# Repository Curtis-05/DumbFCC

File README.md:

<h1 align="center">Dumb FCC</h1>

<p align="center" width="100%">
  
</p>

***

<p align="center">
  
&nbsp; &nbsp; &nbsp; &nbsp;
  
</p>

***

## SPECIFICATIONS

| Parameter | Value | 
| --- | --- |
| Dimensions | 70.0 × 50.0 mm |

***

## DIRECTORY STRUCTURE

    .
    ├─ Computations       # Misc calculations
    ├─ HTML               # HTML files for generated webpage
    ├─ Images             # Pictures and renders
    │
    ├─ kibot_resources    # External resources for KiBot
    │  ├─ colors          # Color theme for KiCad
    │  ├─ fonts           # Fonts used in the project
    │  ├─ scripts         # External scripts used with KiBot
    │  └─ templates       # Templates for KiBot generated reports
    │
    ├─ kibot_yaml         # KiBot YAML config files
    ├─ KiRI               # KiRI (PCB diff viewer) files
    │
    ├─ lib                # KiCad footprint and symbol libraries
    │  ├─ 3d_models       # Component 3D models
    │  ├─ lib_fp          # Footprint libraries
    │  └─ lib_sym         # Symbol libraries
    │
    ├─ Logos              # Logos
    │
    ├─ Manufacturing      # Assembly and fabrication documents
    │  ├─ Assembly        # Assembly documents (BoM, pos, notes)
    │  │
    │  └─ Fabrication     # Fabrication documents (ZIP, notes)
    │     ├─ Drill Tables # CSV drill tables
    │     └─ Gerbers      # Gerbers
    │
    ├─ Report             # Reports for ERC/DRC
    ├─ Schematic          # PDF of schematic
    ├─ Templates          # Title block templates
    ├─ Testing
    │  └─ Testpoints      # Testpoints tables      
    │
    └─ Variants           # Outputs for assembly variants

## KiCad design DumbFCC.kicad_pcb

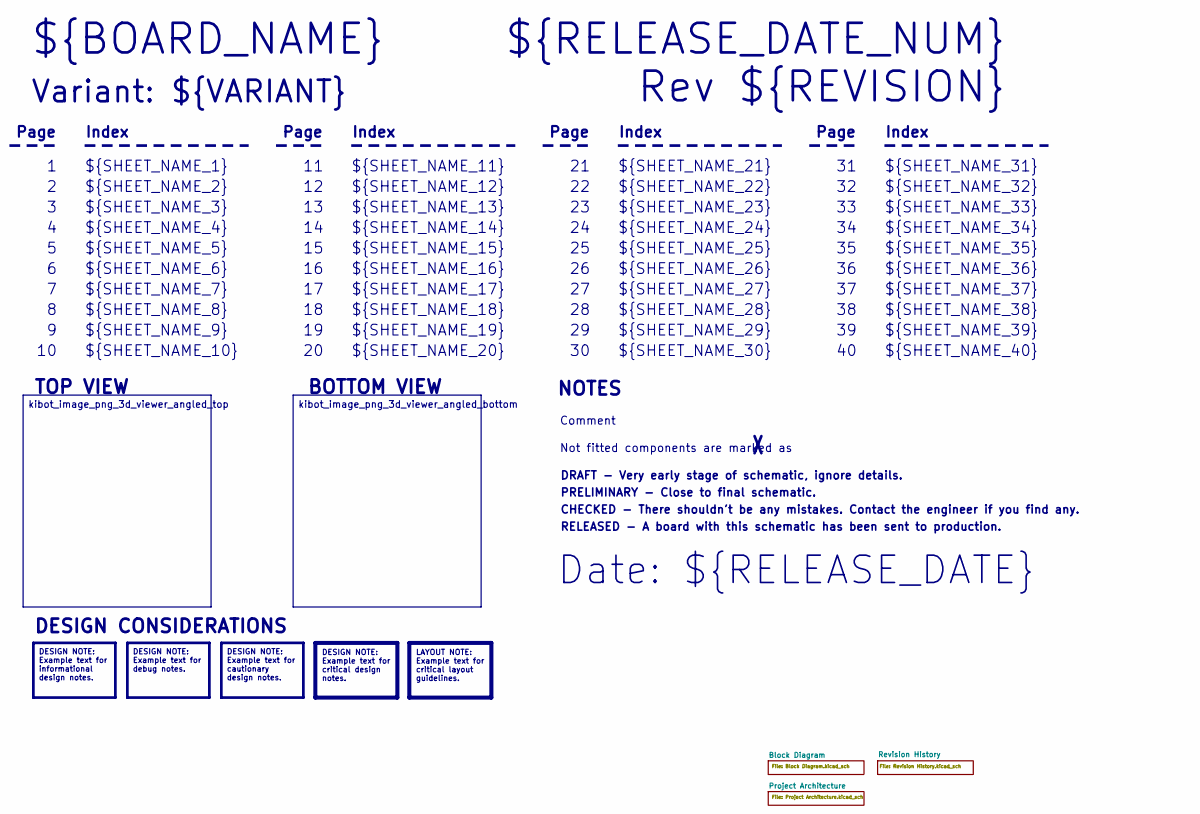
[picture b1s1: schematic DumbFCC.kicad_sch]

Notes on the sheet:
Variant: ${VARIANT}
RELEASED - A board with this schematic has been sent to production.
${SHEET_NAME_24}
Index
Page
PRELIMINARY - Close to final schematic.
${SHEET_NAME_22}
DRAFT - Very early stage of schematic, ignore details.
${SHEET_NAME_12}
${SHEET_NAME_8}
${SHEET_NAME_2}
${SHEET_NAME_5}
${SHEET_NAME_20}
${SHEET_NAME_23}
${RELEASE_DATE_NUM}
${SHEET_NAME_35}
Not fitted components are marked as
${SHEET_NAME_11}
${SHEET_NAME_6}
${SHEET_NAME_37}
${SHEET_NAME_26}
${SHEET_NAME_36}
Rev ${REVISION}
${SHEET_NAME_15}
CHECKED - There shouldn't be any mistakes. Contact the engineer if you find any.
BOTTOM VIEW
${SHEET_NAME_14}
${SHEET_NAME_21}
${SHEET_NAME_17}
${SHEET_NAME_18}
Date: ${RELEASE_DATE}
${SHEET_NAME_7}
${SHEET_NAME_31}
${BOARD_NAME}
NOTES
${SHEET_NAME_40}
${SHEET_NAME_39}
${SHEET_NAME_32}
${SHEET_NAME_1}
${SHEET_NAME_9}

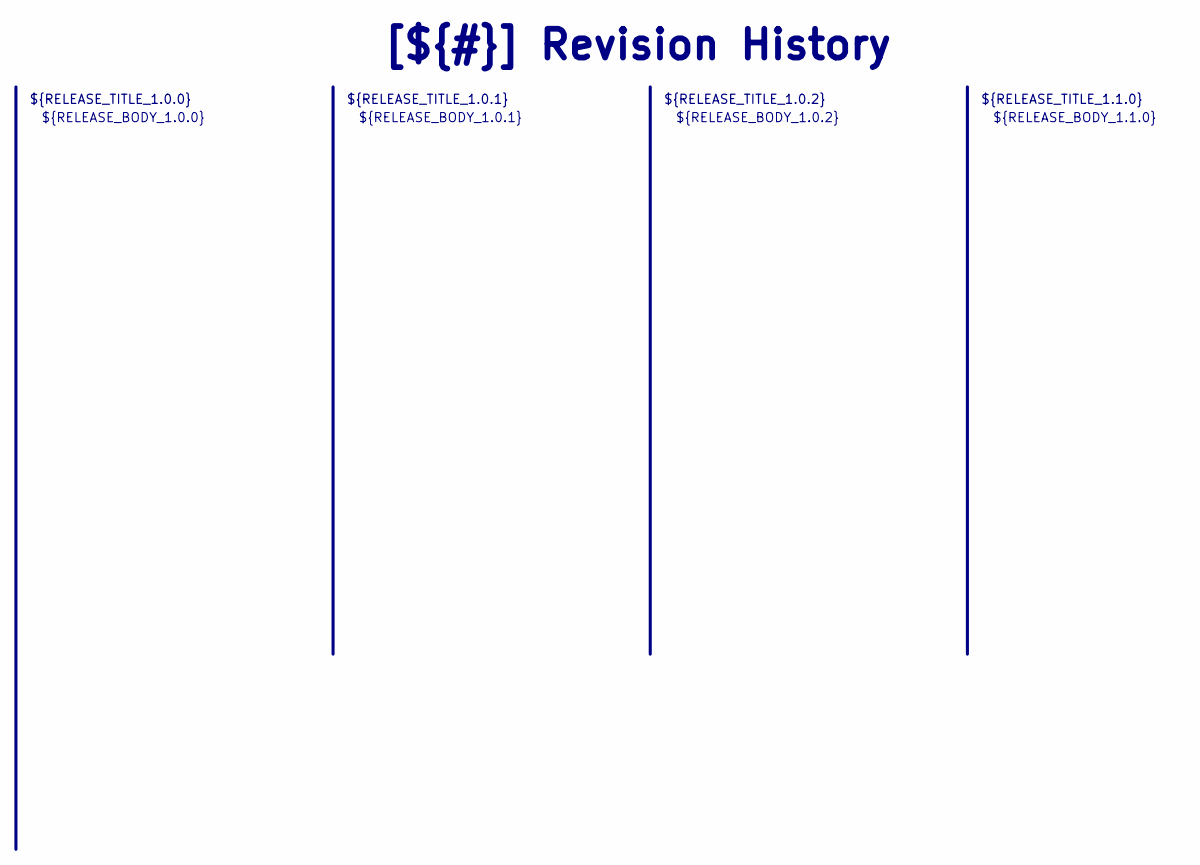
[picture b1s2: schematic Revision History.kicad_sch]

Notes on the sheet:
${RELEASE_BODY_1.1.0}
[${#}] ${TITLE}
${RELEASE_BODY_1.0.0}
${RELEASE_TITLE_1.0.2}
${RELEASE_BODY_1.0.2}
${RELEASE_BODY_1.0.1}
${RELEASE_TITLE_1.0.0}
${RELEASE_TITLE_1.0.1}
${RELEASE_TITLE_1.1.0}

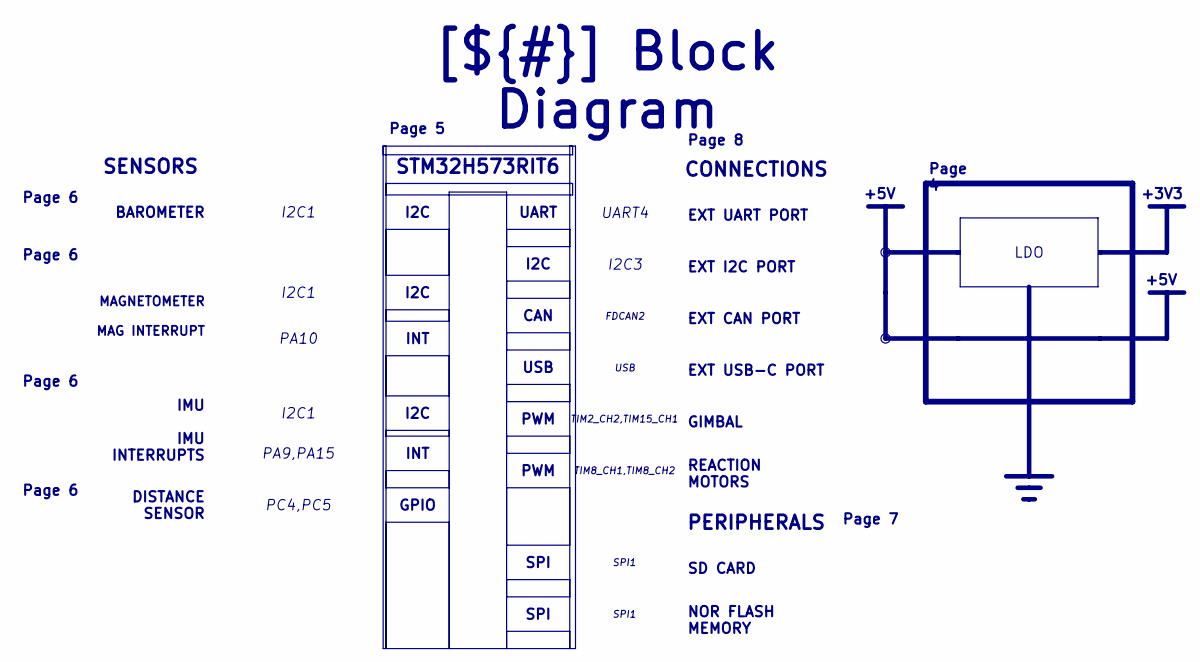
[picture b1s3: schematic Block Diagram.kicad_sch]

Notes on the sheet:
+5V
+3V3
Page 6
SD CARD
Page 5
I2C3
I2C
UART4
SPI1
I2C1
LDO
UART
Page 8
SPI
CAN
PC4,PC5
IMU IMU INTERRUPTS
GPIO
Page 4
TIM2_CH2,TIM15_CH1
EXT CAN PORT
NOR FLASH MEMORY
PA9,PA15
Page 7
PA10
[${#}] ${TITLE}
INT
PERIPHERALS
GIMBAL
FDCAN2
EXT I2C PORT
MAGNETOMETER MAG INTERRUPT
PWM
USB
SENSORS
TIM8_CH1,TIM8_CH2
DISTANCE SENSOR
CONNECTIONS
EXT UART PORT
STM32H573RIT6

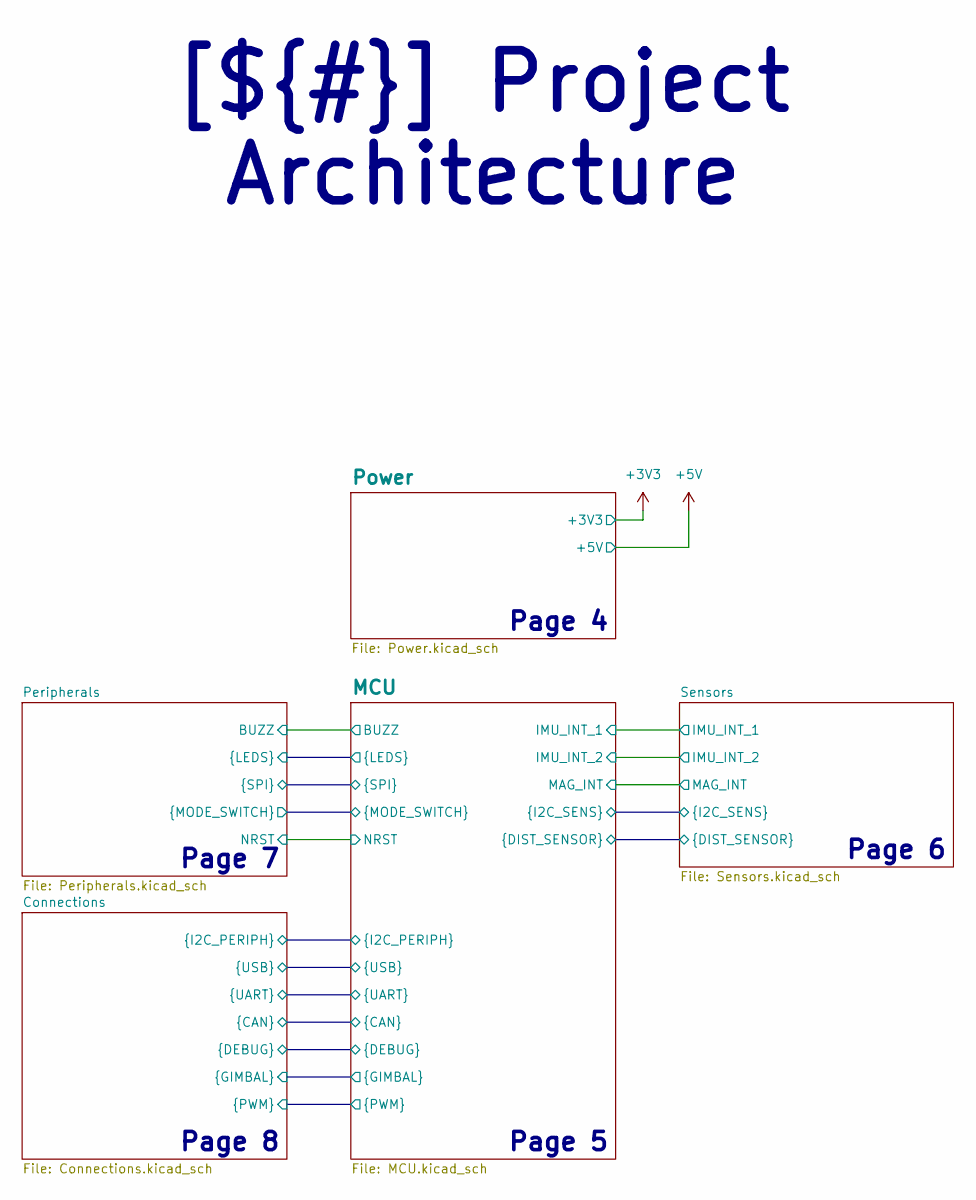
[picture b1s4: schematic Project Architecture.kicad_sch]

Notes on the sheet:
Page 7
Page 8
Page 5
Page 4
Page 6
[${#}] ${TITLE}

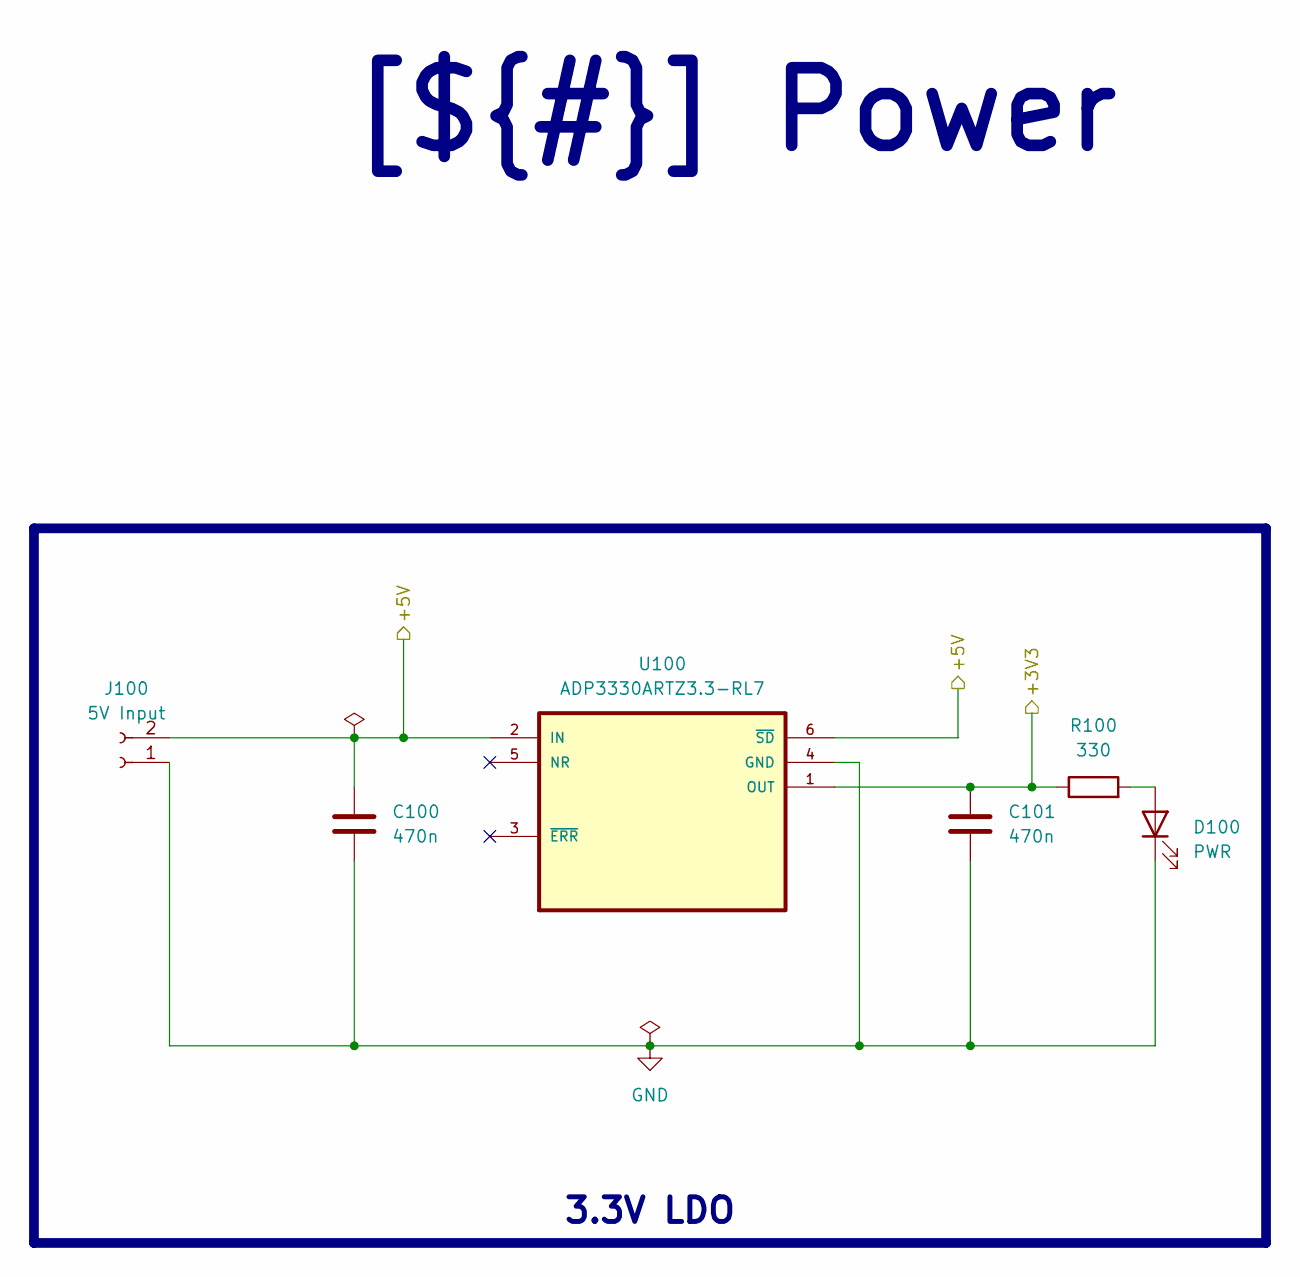
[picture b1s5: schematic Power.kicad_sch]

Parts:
C100, C101: 470n; C_0805_2012Metric
D100: PWR; LED_0805_2012Metric
J100: 5V Input; PinHeader_1x02_P2.54mm_Vertical
R100: 330; R_0805_2012Metric
U100: ADP3330ARTZ3.3-RL7; SOT-23-6

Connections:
+3V3: C101.1, R100.1, U100.1 (OUT); also elsewhere on the board
+5V: C100.1, J100.2, U100.2 (IN), U100.6 (~SD); also elsewhere on the board
GND: C100.2, C101.2, D100.1 (K), J100.1, U100.4 (GND); also elsewhere on the board
unnamed: D100.2 (A), R100.2

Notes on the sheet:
[${#}] ${TITLE}
3.3V LDO

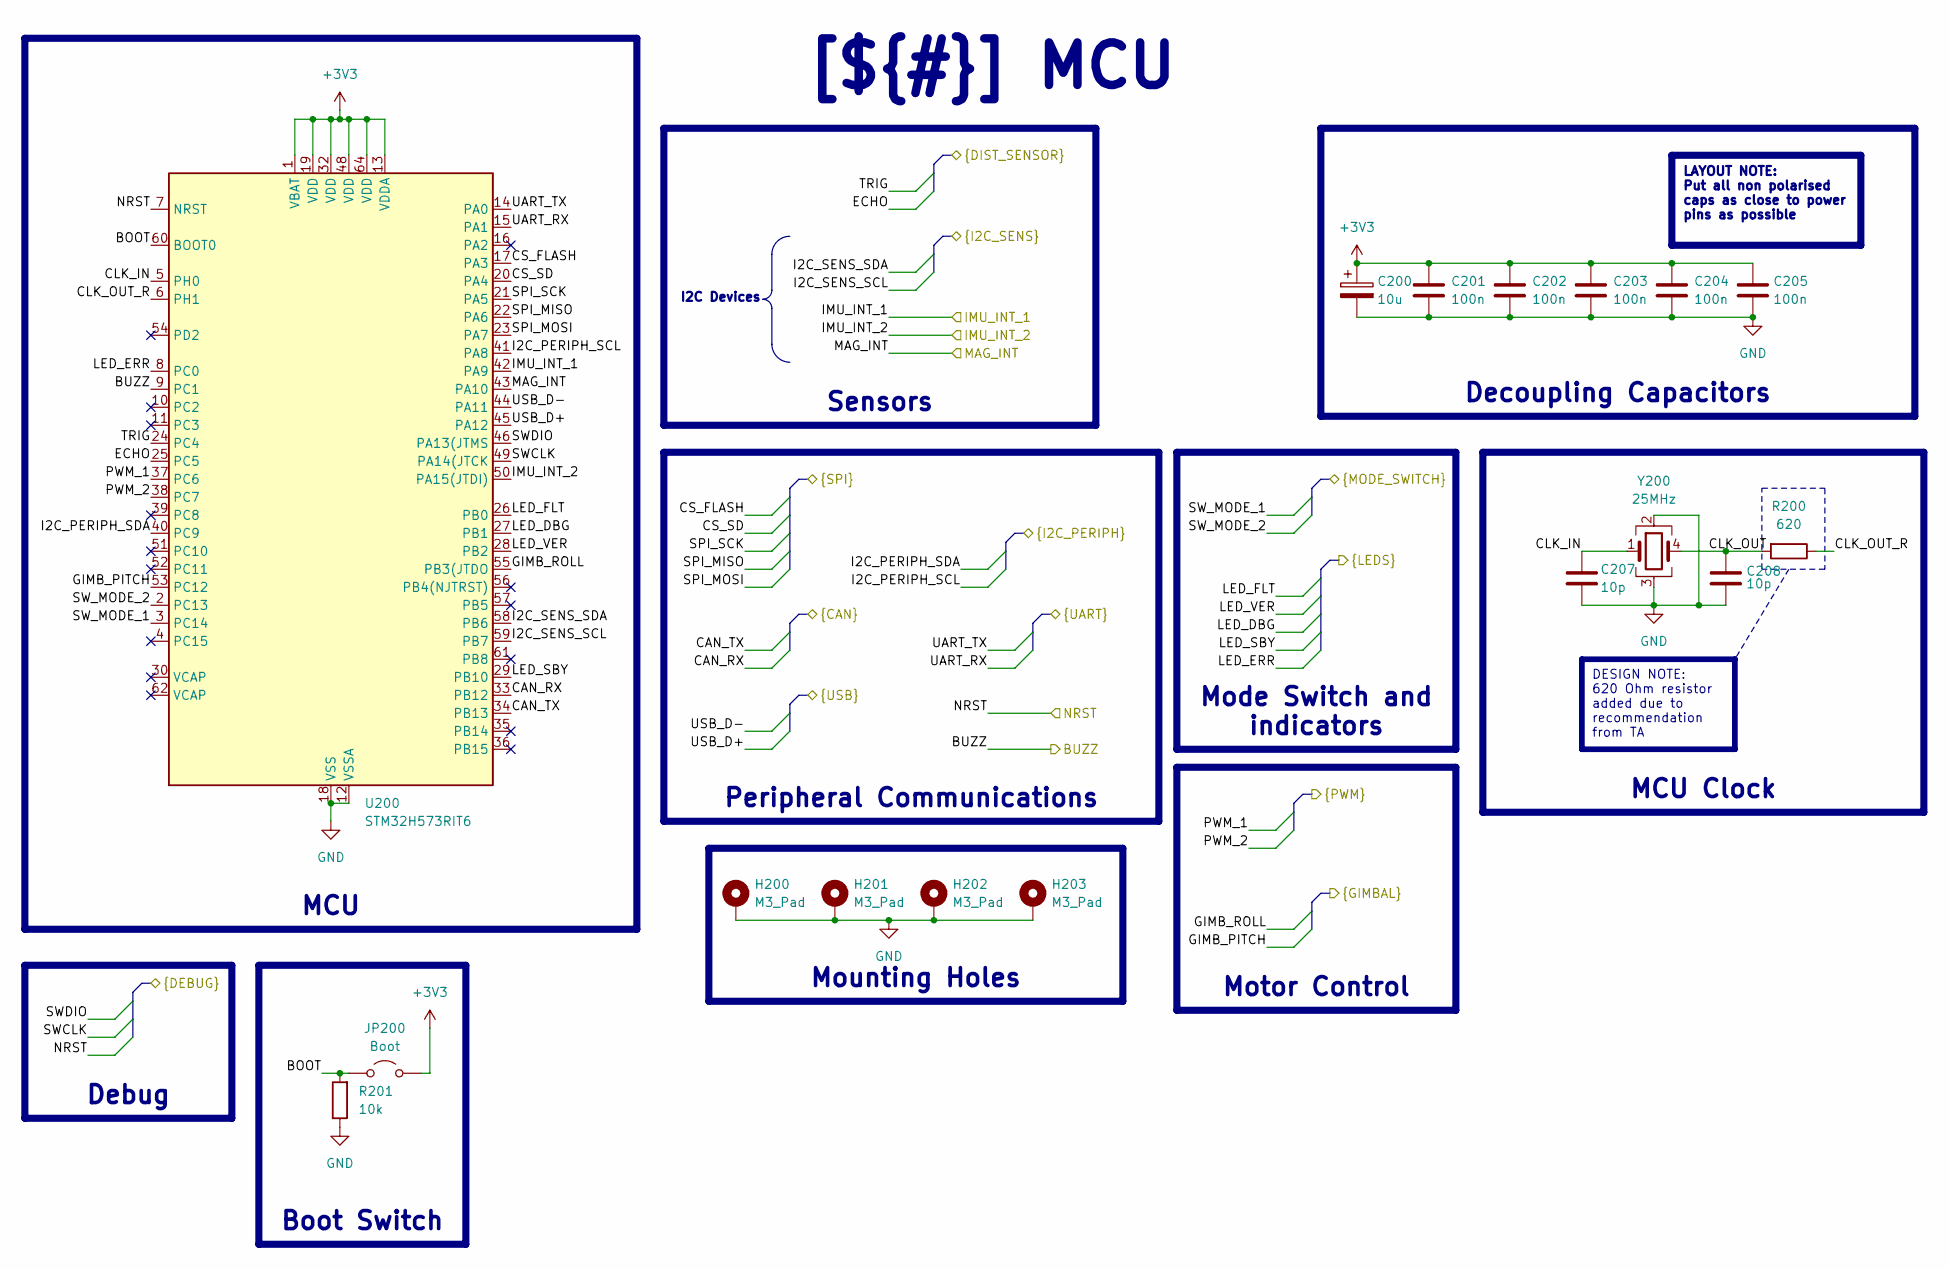
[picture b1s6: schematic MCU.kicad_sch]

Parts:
C200: 10u; CP_Elec_4x5.7
C201, C202, C203, C204, C205: 100n; C_0805_2012Metric
C207, C208: 10p; C_0805_2012Metric
H200, H201, H202, H203: M3_Pad; MountingHole_3.2mm_M3_Pad_TopBottom
JP200: Boot; TestPoint_2Pads_Pitch2.54mm_Drill0.8mm
R200: 620; R_0805_2012Metric
R201: 10k; R_0805_2012Metric
U200: STM32H573RIT6; LQFP-64_10x10mm_P0.5mm
Y200: 25MHz; Crystal_SMD_Abracon_ABM8G-4Pin_3.2x2.5mm

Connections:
+3V3: C200.1, C201.1, C202.1, C203.1, C204.1, C205.1, JP200.2 (B), U200.1 (VBAT), U200.13 (VDDA), U200.19 (VDD), U200.32 (VDD), U200.48 (VDD), U200.64 (VDD); also elsewhere on the board
/Project Architecture/Connections/CAN_RX: U200.33 (PB12); also elsewhere on the board
/Project Architecture/Connections/CAN_TX: U200.34 (PB13); also elsewhere on the board
/Project Architecture/Connections/GIMB_PITCH: U200.53 (PC12); also elsewhere on the board
/Project Architecture/Connections/GIMB_ROLL: U200.55 (PB3(JTDO); also elsewhere on the board
/Project Architecture/Connections/I2C_PERIPH_SCL: U200.41 (PA8); also elsewhere on the board
/Project Architecture/Connections/I2C_PERIPH_SDA: U200.40 (PC9); also elsewhere on the board
/Project Architecture/Connections/NRST: U200.7 (NRST); also elsewhere on the board
/Project Architecture/Connections/PWM_1: U200.37 (PC6); also elsewhere on the board
/Project Architecture/Connections/PWM_2: U200.38 (PC7); also elsewhere on the board
/Project Architecture/Connections/SWCLK: U200.49 (PA14(JTCK); also elsewhere on the board
/Project Architecture/Connections/SWDIO: U200.46 (PA13(JTMS); also elsewhere on the board
/Project Architecture/Connections/UART_RX: U200.15 (PA1); also elsewhere on the board
/Project Architecture/Connections/UART_TX: U200.14 (PA0); also elsewhere on the board
/Project Architecture/Connections/USB_D+: U200.45 (PA12); also elsewhere on the board
/Project Architecture/Connections/USB_D-: U200.44 (PA11); also elsewhere on the board
/Project Architecture/MCU/BOOT: JP200.1 (A), R201.2, U200.60 (BOOT0)
/Project Architecture/MCU/BUZZ: U200.9 (PC1); also elsewhere on the board
/Project Architecture/MCU/CLK_IN: C207.1, U200.5 (PH0), Y200.1
/Project Architecture/MCU/CLK_OUT: C208.1, R200.2, Y200.4
/Project Architecture/MCU/CLK_OUT_R: R200.1, U200.6 (PH1)
/Project Architecture/MCU/CS_FLASH: U200.17 (PA3); also elsewhere on the board
/Project Architecture/MCU/CS_SD: U200.20 (PA4); also elsewhere on the board
/Project Architecture/MCU/ECHO: U200.25 (PC5); also elsewhere on the board
/Project Architecture/MCU/I2C_SENS_SCL: U200.59 (PB7); also elsewhere on the board
/Project Architecture/MCU/I2C_SENS_SDA: U200.58 (PB6); also elsewhere on the board
/Project Architecture/MCU/IMU_INT_1: U200.42 (PA9); also elsewhere on the board
/Project Architecture/MCU/IMU_INT_2: U200.50 (PA15(JTDI)); also elsewhere on the board
/Project Architecture/MCU/LED_DBG: U200.27 (PB1); also elsewhere on the board
/Project Architecture/MCU/LED_ERR: U200.8 (PC0); also elsewhere on the board
/Project Architecture/MCU/LED_FLT: U200.26 (PB0); also elsewhere on the board
/Project Architecture/MCU/LED_SBY: U200.29 (PB10); also elsewhere on the board
/Project Architecture/MCU/LED_VER: U200.28 (PB2); also elsewhere on the board
/Project Architecture/MCU/MAG_INT: U200.43 (PA10); also elsewhere on the board
/Project Architecture/MCU/SPI_MISO: U200.22 (PA6); also elsewhere on the board
/Project Architecture/MCU/SPI_MOSI: U200.23 (PA7); also elsewhere on the board
/Project Architecture/MCU/SPI_SCK: U200.21 (PA5); also elsewhere on the board
/Project Architecture/MCU/SW_MODE_1: U200.3 (PC14); also elsewhere on the board
/Project Architecture/MCU/SW_MODE_2: U200.2 (PC13); also elsewhere on the board
/Project Architecture/MCU/TRIG: U200.24 (PC4); also elsewhere on the board
GND: C200.2, C201.2, C202.2, C203.2, C204.2, C205.2, C207.2, C208.2, H200.1, H201.1, H202.1, H203.1, R201.1, U200.12 (VSSA), U200.18 (VSS), U200.31 (VSS), U200.47 (VSS), U200.63 (VSS), Y200.2, Y200.3; also elsewhere on the board

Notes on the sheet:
DESIGN NOTE: 620 Ohm resistor added due to recommendation from TA
Sensors
Debug
Mode Switch and indicators
Peripheral Communications
Mounting Holes
LAYOUT NOTE: Put all non polarised caps as close to power pins as possible
[${#}] ${TITLE}
Boot Switch
I2C Devices
Motor Control
MCU Clock
MCU
Decoupling Capacitors

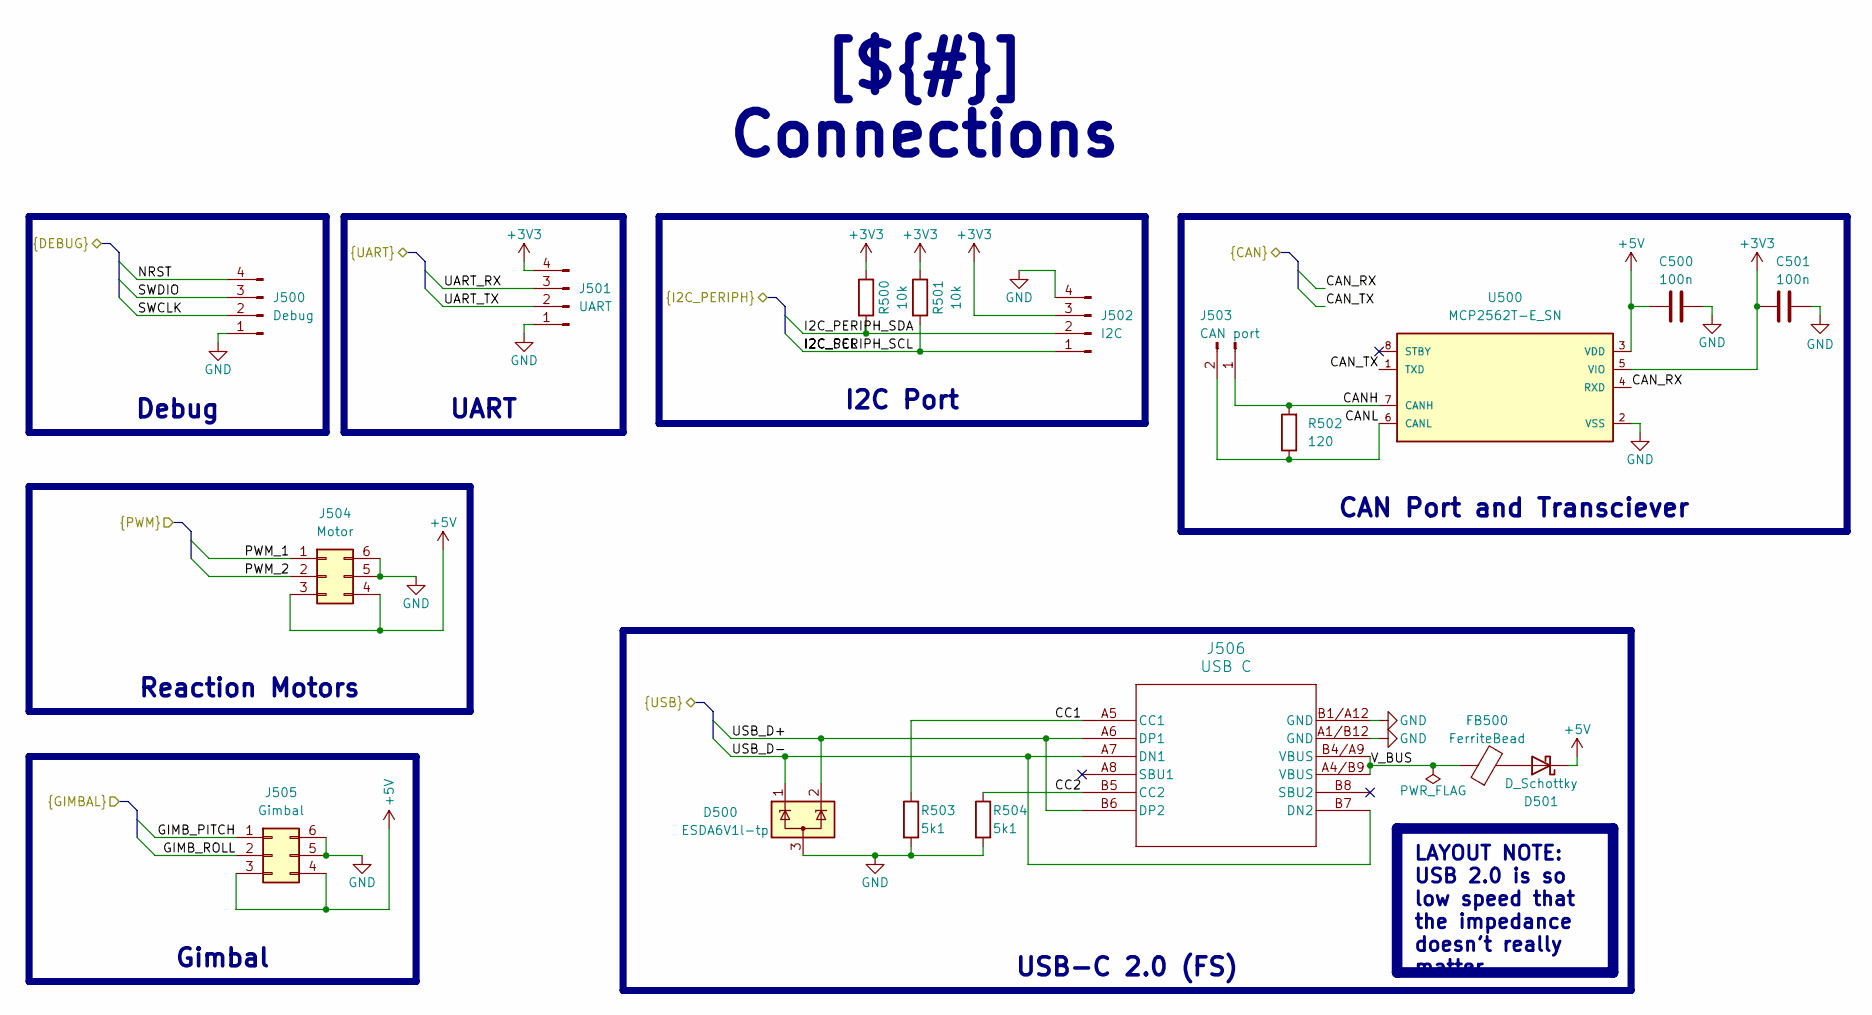
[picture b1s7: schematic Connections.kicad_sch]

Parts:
C500, C501: 100n; C_0805_2012Metric
D500: ESDA6V1l-tp; SOT-23-3
D501: D_Schottky; P25_DO-214AC_SMA
FB500: FerriteBead; L_0805_2012Metric
J500: Debug; PinHeader_1x04_P2.54mm_Vertical
J501: UART; PinHeader_1x04_P2.54mm_Vertical
J502: I2C; PinHeader_1x04_P2.54mm_Vertical
J503: CAN port; PinHeader_1x02_P2.54mm_Vertical
J504: Motor; PinHeader_2x03_P2.54mm_Vertical
J505: Gimbal; PinHeader_2x03_P2.54mm_Vertical
J506: USB C; 2171790001_MOL
R500, R501: 10k; R_0805_2012Metric
R502: 120; R_0805_2012Metric
R503, R504: 5k1; R_0805_2012Metric
U500: MCP2562T-E_SN; SOIC-8_3.9x4.9mm_P1.27mm

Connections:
+3V3: C501.2, J501.4, J502.3, R500.1, R501.1, U500.5 (VIO); also elsewhere on the board
+5V: C500.2, D501.1 (K), J504.3, J504.4, J505.3, J505.4, U500.3 (VDD); also elsewhere on the board
/Project Architecture/Connections/CANH: J503.1, R502.2, U500.7 (CANH)
/Project Architecture/Connections/CANL: J503.2, R502.1, U500.6 (CANL)
/Project Architecture/Connections/CAN_RX: U500.4 (RXD); also elsewhere on the board
/Project Architecture/Connections/CAN_TX: U500.1 (TXD); also elsewhere on the board
/Project Architecture/Connections/CC1: J506.A5 (CC1), R503.1
/Project Architecture/Connections/CC2: J506.B5 (CC2), R504.1
/Project Architecture/Connections/GIMB_PITCH: J505.1; also elsewhere on the board
/Project Architecture/Connections/GIMB_ROLL: J505.2; also elsewhere on the board
/Project Architecture/Connections/I2C_PERIPH_SCL: J502.1, R501.2; also elsewhere on the board
/Project Architecture/Connections/I2C_PERIPH_SDA: J502.2, R500.2; also elsewhere on the board
/Project Architecture/Connections/NRST: J500.4; also elsewhere on the board
/Project Architecture/Connections/PWM_1: J504.1; also elsewhere on the board
/Project Architecture/Connections/PWM_2: J504.2; also elsewhere on the board
/Project Architecture/Connections/SWCLK: J500.2; also elsewhere on the board
/Project Architecture/Connections/SWDIO: J500.3; also elsewhere on the board
/Project Architecture/Connections/UART_RX: J501.3; also elsewhere on the board
/Project Architecture/Connections/UART_TX: J501.2; also elsewhere on the board
/Project Architecture/Connections/USB_D+: D500.2 (K), J506.A6 (DP1), J506.B6 (DP2); also elsewhere on the board
/Project Architecture/Connections/USB_D-: D500.1 (K), J506.A7 (DN1), J506.B7 (DN2); also elsewhere on the board
/Project Architecture/Connections/V_BUS: FB500.1, J506.A4/B9 (VBUS), J506.B4/A9 (VBUS)
GND: C500.1, C501.1, D500.3 (A), J500.1, J501.1, J502.4, J504.5, J504.6, J505.5, J505.6, J506.A1/B12 (GND), J506.B1/A12 (GND), R503.2, R504.2, U500.2 (VSS); also elsewhere on the board
unnamed: D501.2 (A), FB500.2

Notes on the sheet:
USB-C 2.0 (FS)
Reaction Motors
I2C Port
Debug
Gimbal
[${#}] ${TITLE}
LAYOUT NOTE: USB 2.0 is so low speed that the impedance doesn't really matter
CAN Port and Transciever
UART

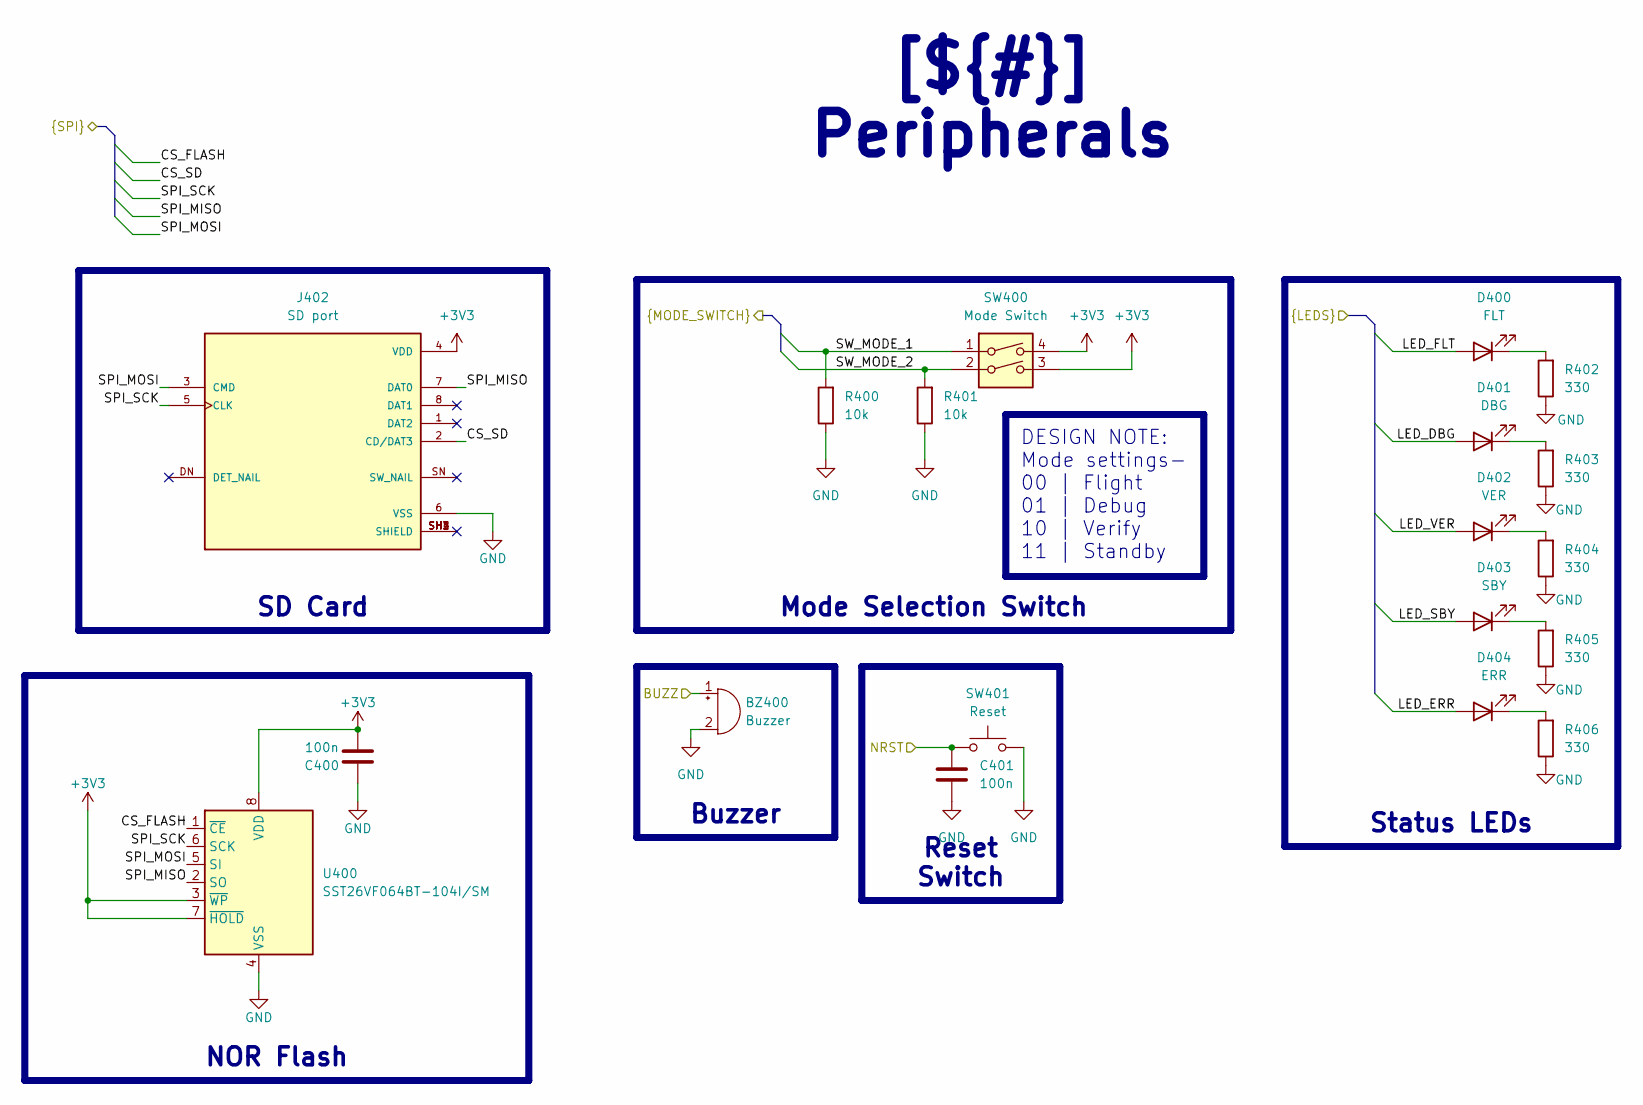
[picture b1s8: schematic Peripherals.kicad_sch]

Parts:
BZ400: Buzzer; XDCR_AI-1027-TWT-3V-R
C400, C401: 100n; C_0805_2012Metric
D400: FLT; LED_0805_2012Metric
D401: DBG; LED_0805_2012Metric
D402: VER; LED_0805_2012Metric
D403: SBY; LED_0805_2012Metric
D404: ERR; LED_0805_2012Metric
J402: SD port; MOLEX_5027740891
R400, R401: 10k; R_0805_2012Metric
R402, R403, R404, R405, R406: 330; R_0805_2012Metric
SW400: Mode Switch; SW_DS04-254-1-02BK-SMT
SW401: Reset; DTS32NVB
U400: SST26VF064BT-104I/SM; SOIC-8_5.3x5.3mm_P1.27mm

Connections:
+3V3: C400.1, J402.4 (VDD), SW400.3, SW400.4, U400.3 (~WP), U400.7 (~HOLD), U400.8 (VDD); also elsewhere on the board
/Project Architecture/Connections/NRST: C401.1, SW401.1; also elsewhere on the board
/Project Architecture/MCU/BUZZ: BZ400.1 (+); also elsewhere on the board
/Project Architecture/MCU/CS_FLASH: U400.1 (~CE); also elsewhere on the board
/Project Architecture/MCU/CS_SD: J402.2 (CD/DAT3); also elsewhere on the board
/Project Architecture/MCU/LED_DBG: D401.2 (A); also elsewhere on the board
/Project Architecture/MCU/LED_ERR: D404.2 (A); also elsewhere on the board
/Project Architecture/MCU/LED_FLT: D400.2 (A); also elsewhere on the board
/Project Architecture/MCU/LED_SBY: D403.2 (A); also elsewhere on the board
/Project Architecture/MCU/LED_VER: D402.2 (A); also elsewhere on the board
/Project Architecture/MCU/SPI_MISO: J402.7 (DAT0), U400.2 (SO); also elsewhere on the board
/Project Architecture/MCU/SPI_MOSI: J402.3 (CMD), U400.5 (SI); also elsewhere on the board
/Project Architecture/MCU/SPI_SCK: J402.5 (CLK), U400.6 (SCK); also elsewhere on the board
/Project Architecture/MCU/SW_MODE_1: R400.2, SW400.1; also elsewhere on the board
/Project Architecture/MCU/SW_MODE_2: R401.2, SW400.2; also elsewhere on the board
GND: BZ400.2 (-), C400.2, C401.2, J402.6 (VSS), R400.1, R401.1, R402.1, R403.1, R404.1, R405.1, R406.1, SW401.2, U400.4 (VSS); also elsewhere on the board
unnamed: D400.1 (K), R402.2
unnamed: D401.1 (K), R403.2
unnamed: D402.1 (K), R404.2
unnamed: D403.1 (K), R405.2
unnamed: D404.1 (K), R406.2

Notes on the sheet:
[${#}] ${TITLE}
Status LEDs
SD Card
Reset Switch
Mode Selection Switch
DESIGN NOTE: Mode settings- 00 | Flight 01 | Debug 10 | Verify 11 | Standby
NOR Flash
Buzzer

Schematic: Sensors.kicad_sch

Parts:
C300, C304, C305, C306, C308: 100n; C_0805_2012Metric
C303: 220n; C_0805_2012Metric
C307: 10u; CP_Elec_4x5.7
J300: Distance Sensor; PinHeader_1x04_P2.54mm_Vertical
JP300, JP302: SD0; SolderJumper-2_P1.3mm_Open_TrianglePad1.0x1.5mm
R300, R301, R302, R303: 10k; R_0805_2012Metric
TP300: SDA; TestPoint_Pad_D1.5mm
TP301: SCL; TestPoint_Pad_D1.5mm
U300: LIS2MDL; LGA-12_2x2mm_P0.5mm
U301: LSM6DSL; LGA-14_3x2.5mm_P0.5mm_LayoutBorder3x4y
U302: MS5607-02BA; LGA-8_3x5mm_P1.25mm

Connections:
+3V3: C300.2, C304.2, C305.1, C306.1, C307.1, C308.1, R300.1, R301.1, R302.1, R303.1, U300.3 (~CS), U300.9 (Vdd), U300.10 (Vdd_IO), U301.5 (VDDIO), U301.8 (VDD), U301.12 (CS), U302.1 (VDD), U302.2 (PS); also elsewhere on the board
+5V: J300.4; also elsewhere on the board
/Project Architecture/MCU/ECHO: J300.2; also elsewhere on the board
/Project Architecture/MCU/I2C_SENS_SCL: R303.2, TP301.1, U300.1 (SCL/SPC), U301.13 (SCL), U302.8 (SCLK); also elsewhere on the board
/Project Architecture/MCU/I2C_SENS_SDA: R302.2, TP300.1, U300.4 (SDA/SDI/SDO), U301.14 (SDA), U302.7 (SDI/SDA); also elsewhere on the board
/Project Architecture/MCU/IMU_INT_1: U301.4 (INT1); also elsewhere on the board
/Project Architecture/MCU/IMU_INT_2: U301.9 (INT2); also elsewhere on the board
/Project Architecture/MCU/MAG_INT: U300.7 (DRDY); also elsewhere on the board
/Project Architecture/MCU/TRIG: J300.3; also elsewhere on the board
GND: C300.1, C303.2, C304.1, C305.2, C306.2, C307.2, C308.2, J300.1, JP300.1 (A), JP302.1 (A), U300.6 (GND), U300.8 (GND), U301.2 (SDX), U301.3 (SCX), U301.6 (GND), U301.7 (GND), U302.3 (GND), U302.4 (CSB), U302.5 (CSB); also elsewhere on the board
unnamed: JP300.2 (B), R300.2, U301.1 (SDO/SA0)
unnamed: JP302.2 (B), R301.2, U302.6 (SDO)
unnamed: C303.1, U300.5 (C1)

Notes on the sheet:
Test Points
I2C Bus Pull-up Resistors
[${#}] ${TITLE}
DESIGN NOTE: IMU address: 110101 + !SDO + R/W bit Magnetometer address: 0011110 + R/W bit Barometer address: 111011 + SDO + R/W bit
Barometer
Distance Sensor
DESIGN NOTE: The Jumper can be used to change the I2C address
Magnetometer
LAYOUT NOTE: Route I2C Lines through resistors to minimise stubs
Inertial Measurement Unit
DESIGN NOTE: Logic for this pin is flipped
